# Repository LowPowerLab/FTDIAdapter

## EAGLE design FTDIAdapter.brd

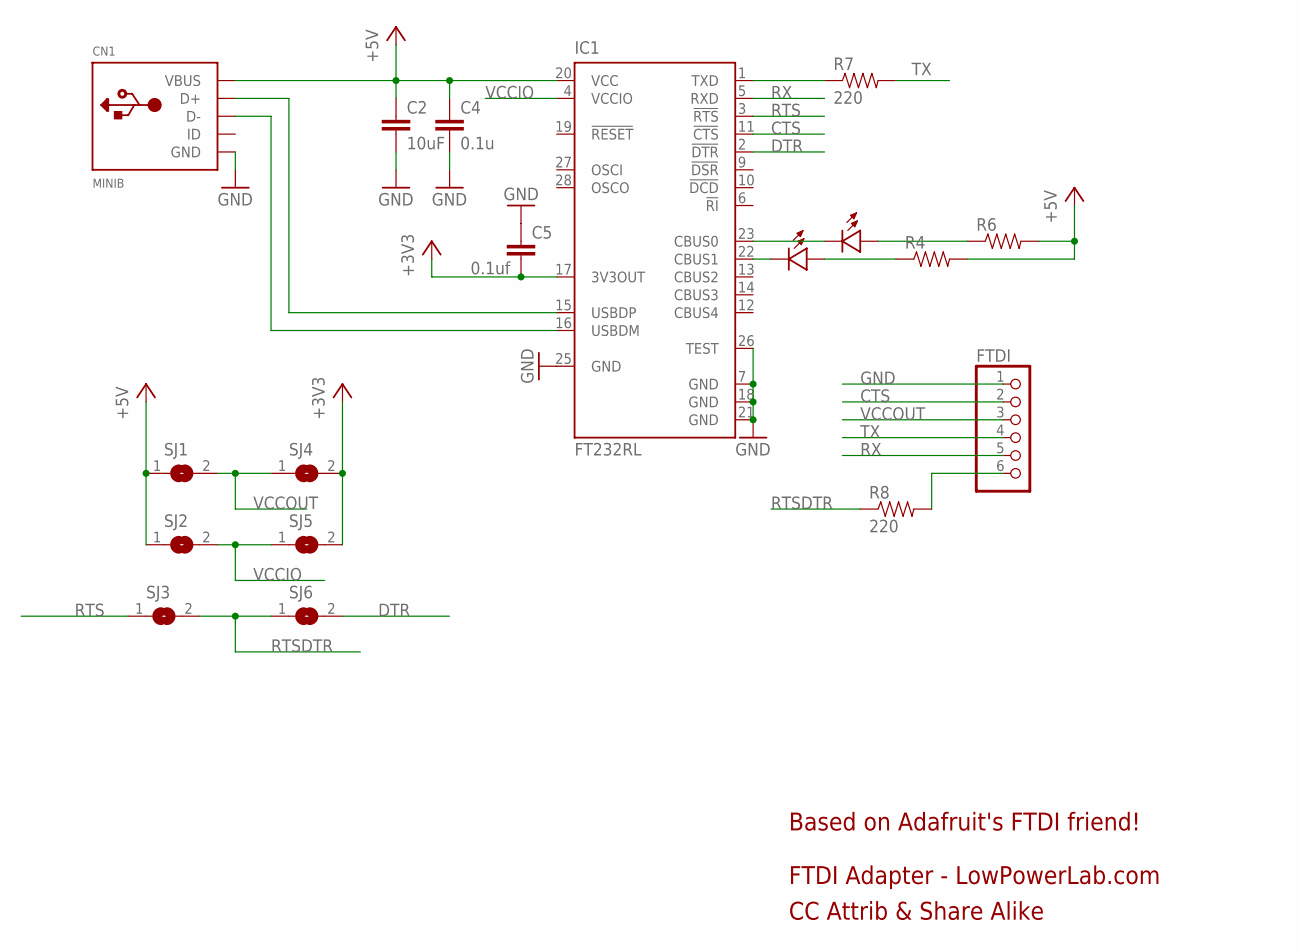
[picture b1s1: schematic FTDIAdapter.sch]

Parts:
C2: 10uF; 0805-CAP-LARGEPADS
C4: 0.1u; 0603-CAP
C5: 0.1uf; 0603-CAP
CN1: MINIB; USB-MINIB
FTDI: PINHD-1X6CB; 1X06-CLEANBIG
IC1: FT232RL; SSOP28
R4, R6: RESISTOR0603-RES; 0603-RES
R7, R8: 220; 0603-RES
SJ1, SJ2, SJ3, SJ4, SJ5, SJ6: SJ
U$4, U$5: LED0603; 0603-LED

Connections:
+3V3: C5.2, IC1.17 (3V3OUT), SJ4.2, SJ5.2
+5V: C2.1, C4.1, CN1.VBUS, IC1.20 (VCC), R4.2, R6.2, SJ1.1, SJ2.1
CTS: FTDI.2, IC1.11 (!CTS)
DTR: IC1.2 (!DTR), SJ6.2
GND: C2.2, C4.2, C5.1, CN1.GND, FTDI.1, IC1.7 (GND), IC1.18 (GND), IC1.21 (GND), IC1.25 (GND), IC1.26 (TEST)
unnamed: FTDI.6, R8.2
unnamed: CN1.D+, IC1.15 (USBDP)
unnamed: CN1.D-, IC1.16 (USBDM)
unnamed: IC1.1 (TXD), R7.1
unnamed: IC1.23 (CBUS0), U$4.MINUS
unnamed: IC1.22 (CBUS1), U$5.MINUS
unnamed: R4.1, U$5.PLUS
unnamed: R6.1, U$4.PLUS
RTS: IC1.3 (!RTS), SJ3.1
RTSDTR: R8.1, SJ3.2, SJ6.1
RX: FTDI.5, IC1.5 (RXD)
TX: FTDI.4, R7.2
VCCIO: IC1.4 (VCCIO), SJ2.2, SJ5.1
VCCOUT: FTDI.3, SJ1.2, SJ4.1

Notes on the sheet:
CC Attrib & Share Alike
FTDI Adapter - LowPowerLab.com
Based on Adafruit's FTDI friend!

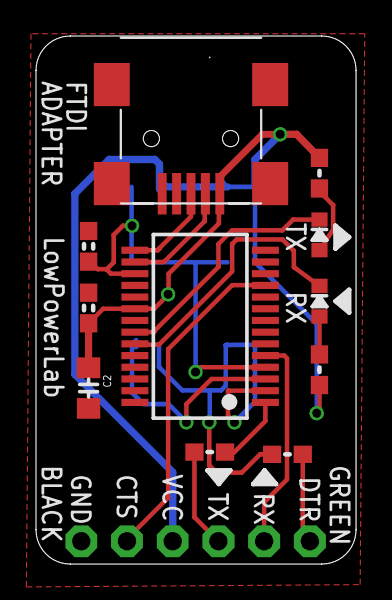
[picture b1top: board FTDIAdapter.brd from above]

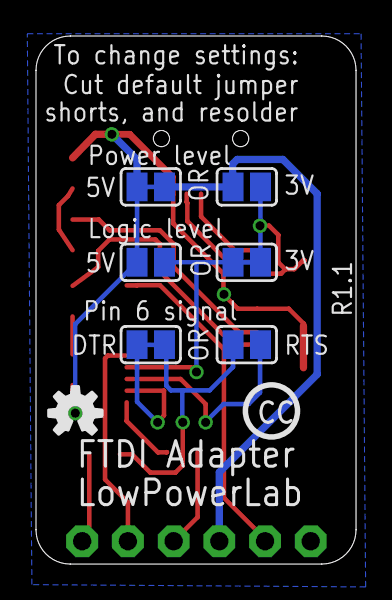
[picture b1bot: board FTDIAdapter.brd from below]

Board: 2 copper layers, 17.8 x 29.3 mm, 19 parts (7 on the bottom side), 19 nets.

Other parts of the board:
U$3: OSHW-LOGO-S

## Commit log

2014-01-21 Add them files
2014-01-21 Remove MFGCode

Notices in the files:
parts and their libraries:
SparkFun-Aesthetics: Licensing: CC v3.0 Share-Alike You are welcome to use this library for commercial purposes.
